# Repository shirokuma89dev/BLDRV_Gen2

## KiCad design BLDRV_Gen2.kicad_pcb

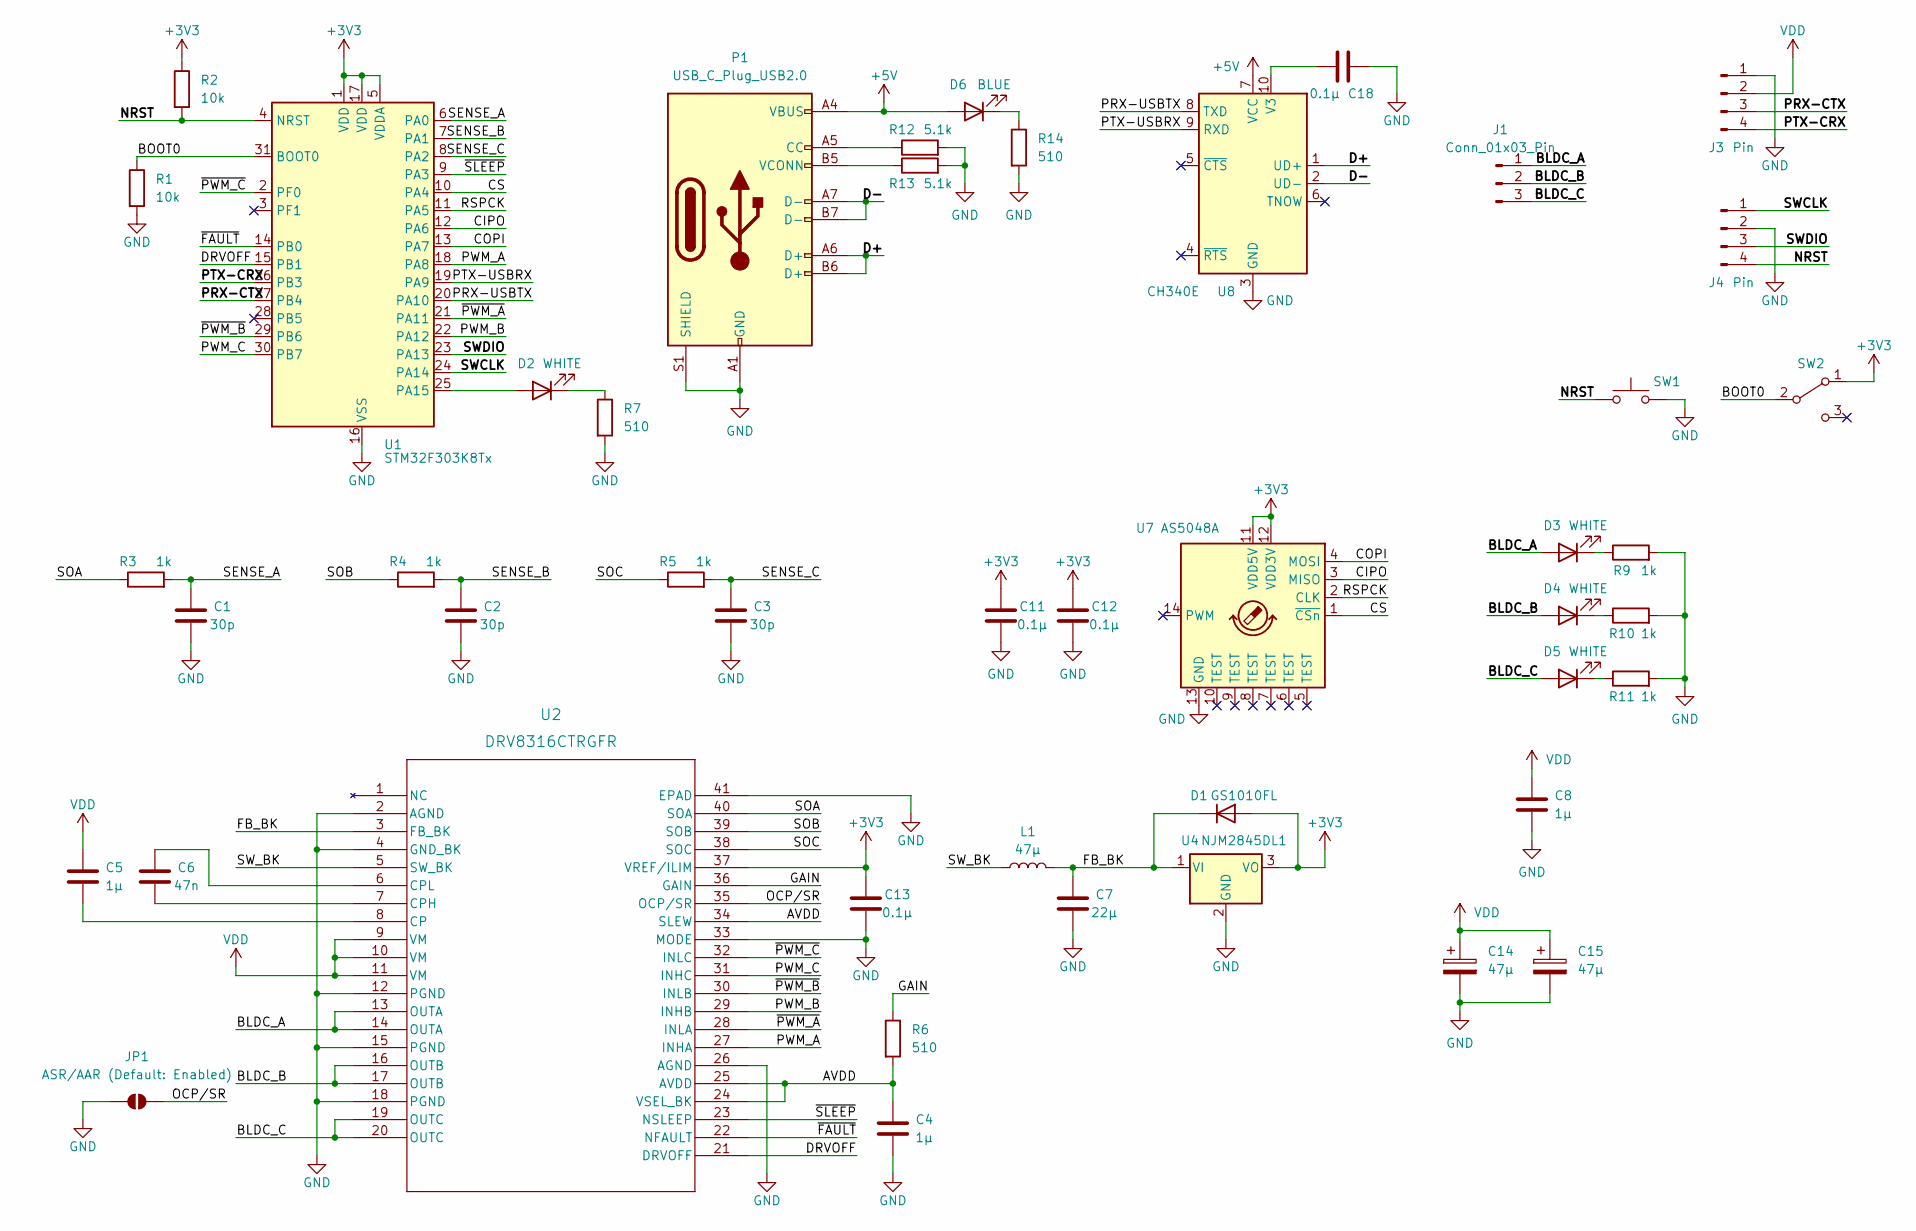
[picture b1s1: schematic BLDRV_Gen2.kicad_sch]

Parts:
C1, C2, C3: 30p; C_0603_1608Metric
C4, C5: 1μ; C_0603_1608Metric
C6: 47n; C_0603_1608Metric
C7: 22µ; C_0603_1608Metric
C8: 1µ; C_0603_1608Metric
C11, C12, C13, C18: 0.1µ; C_0603_1608Metric
C14, C15: 47μ; CP_Elec_5x5.3
D1: GS1010FL; D_SOD-123
D2, D3, D4, D5: WHITE; LED_0603_1608Metric
D6: BLUE; LED_0603_1608Metric
J1: Conn_01x03_Pin; Molex_SPOX_5268-03A_1x03_P2.50mm_Horizontal
J3: Pin; Molex_SPOX_5268-04A_1x04_P2.50mm_Horizontal
J4: Pin; PinHeader_1x04_P1.00mm_Vertical
JP1: ASR/AAR (Default: Enabled); SolderJumper-2_P1.3mm_Open_TrianglePad1.0x1.5mm
L1: 47μ; L_6.3x6.3_H3
P1: USB_C_Plug_USB2.0; USB_C_Receptacle_HCTL_HC-TYPE-C-16P-01A
R1, R2: 10k; R_0402_1005Metric
R3, R4, R5, R9, R10, R11: 1k; R_0402_1005Metric
R6, R7, R14: 510; R_0402_1005Metric
R12, R13: 5.1k; R_0402_1005Metric
SW1: SW_Push; SW_PUSH_6mm
SW2: SW_SPDT; SW_Slide_SPDT_Angled_CK_OS102011MA1Q
U1: STM32F303K8Tx; LQFP-32_7x7mm_P0.8mm
U2: DRV8316CTRGFR; VQFN40_RGF_TEX
U4: NJM2845DL1; TO-252-2
U7: AS5048A; TSSOP-14_4.4x5mm_P0.65mm
U8: CH340E; MSOP-10_3x3mm_P0.5mm

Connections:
+3V3: C11.2, C12.2, C13.2, D1.2 (A), R2.1, SW2.1 (A), U1.1 (VDD), U1.5 (VDDA), U1.17 (VDD), U2.37 (VREF/ILIM), U4.3 (VO), U7.11 (VDD5V), U7.12 (VDD3V)
+5V: D6.2 (A), P1.A4 (VBUS), P1.A9 (VBUS), P1.B4 (VBUS), P1.B9 (VBUS), U8.7 (VCC)
/AVDD: C4.2, R6.2, U2.24 (VSEL_BK), U2.25 (AVDD), U2.34 (SLEW)
/BLDC_A: D3.2 (A), J1.1, U2.13 (OUTA), U2.14 (OUTA)
/BLDC_B: D4.2 (A), J1.2, U2.16 (OUTB), U2.17 (OUTB)
/BLDC_C: D5.2 (A), J1.3, U2.19 (OUTC), U2.20 (OUTC)
/BOOT0: R1.1, SW2.2 (B), U1.31 (BOOT0)
/CIPO: U1.12 (PA6), U7.3 (MISO)
/COPI: U1.13 (PA7), U7.4 (MOSI)
/CS: U1.10 (PA4), U7.1 (~CSn)
/D+: P1.A6 (D+), P1.B6 (D+), U8.1 (UD+)
/D-: P1.A7 (D-), P1.B7 (D-), U8.2 (UD-)
/DRVOFF: U1.15 (PB1), U2.21 (DRVOFF)
/FB_BK: C7.2, D1.1 (K), L1.2, U2.3 (FB_BK), U4.1 (VI)
/GAIN: R6.1, U2.36 (GAIN)
/NRST: J4.4, R2.2, SW1.1, U1.4 (NRST)
/OCP/SR: JP1.2 (B), U2.35 (OCP/SR)
/PRX-CTX: J3.3, U1.27 (PB4)
/PRX-USBTX: U1.20 (PA10), U8.8 (TXD)
/PTX-CRX: J3.4, U1.26 (PB3)
/PTX-USBRX: U1.19 (PA9), U8.9 (RXD)
/PWM_A: U1.18 (PA8), U2.27 (INHA)
/PWM_B: U1.22 (PA12), U2.29 (INHB)
/PWM_C: U1.30 (PB7), U2.31 (INHC)
/RSPCK: U1.11 (PA5), U7.2 (CLK)
/SENSE_A: C1.2, R3.2, U1.6 (PA0)
/SENSE_B: C2.2, R4.2, U1.7 (PA1)
/SENSE_C: C3.2, R5.2, U1.8 (PA2)
/SOA: R3.1, U2.40 (SOA)
/SOB: R4.1, U2.39 (SOB)
/SOC: R5.1, U2.38 (SOC)
/SWCLK: J4.1, U1.24 (PA14)
/SWDIO: J4.3, U1.23 (PA13)
/SW_BK: L1.1, U2.5 (SW_BK)
/~FAULT: U1.14 (PB0), U2.22 (NFAULT)
/~PWM_A: U1.21 (PA11), U2.28 (INLA)
/~PWM_B: U1.29 (PB6), U2.30 (INLB)
/~PWM_C: U1.2 (PF0), U2.32 (INLC)
/~SLEEP: U1.9 (PA3), U2.23 (NSLEEP)
GND: C1.1, C2.1, C3.1, C4.1, C7.1, C8.1, C11.1, C12.1, C13.1, C14.2, C15.2, C18.2, J3.1, J4.2, JP1.1 (A), P1.A1 (GND), P1.A12 (GND), P1.B1 (GND), P1.B12 (GND), P1.S1 (SHIELD), R1.2, R7.2, R9.2, R10.2, R11.2, R12.2, R13.2, R14.2, SW1.2, U1.16 (VSS), U1.32 (VSS), U2.2 (AGND), U2.4 (GND_BK), U2.12 (PGND), U2.15 (PGND), U2.18 (PGND), U2.26 (AGND), U2.33 (MODE), U2.41 (EPAD), U4.2 (GND), U7.13 (GND), U8.3 (GND)
unnamed: D2.2 (A), U1.25 (PA15)
unnamed: D2.1 (K), R7.1
unnamed: D3.1 (K), R9.1
unnamed: D4.1 (K), R10.1
unnamed: D5.1 (K), R11.1
unnamed: D6.1 (K), R14.1
unnamed: P1.A5 (CC), R12.1
unnamed: P1.B5 (VCONN), R13.1
unnamed: C5.1, U2.8 (CP)
unnamed: C6.1, U2.7 (CPH)
unnamed: C6.2, U2.6 (CPL)
unnamed: C18.1, U8.10 (V3)
VDD: C5.2, C8.2, C14.1, C15.1, J3.2, U2.9 (VM), U2.10 (VM), U2.11 (VM)

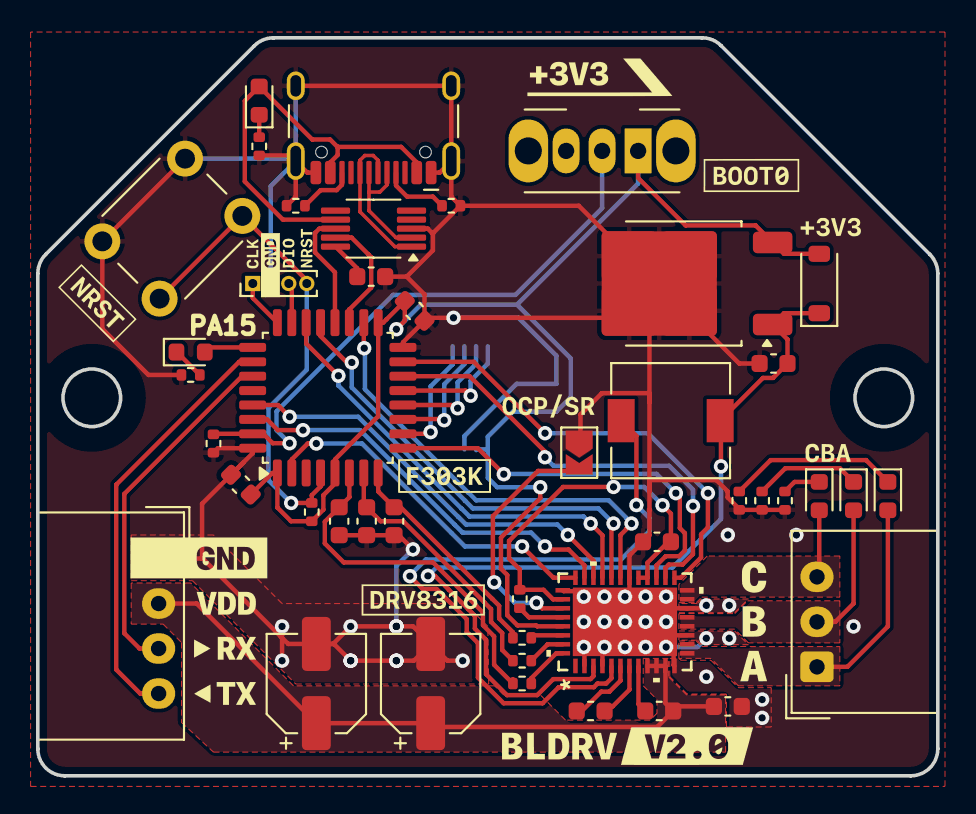
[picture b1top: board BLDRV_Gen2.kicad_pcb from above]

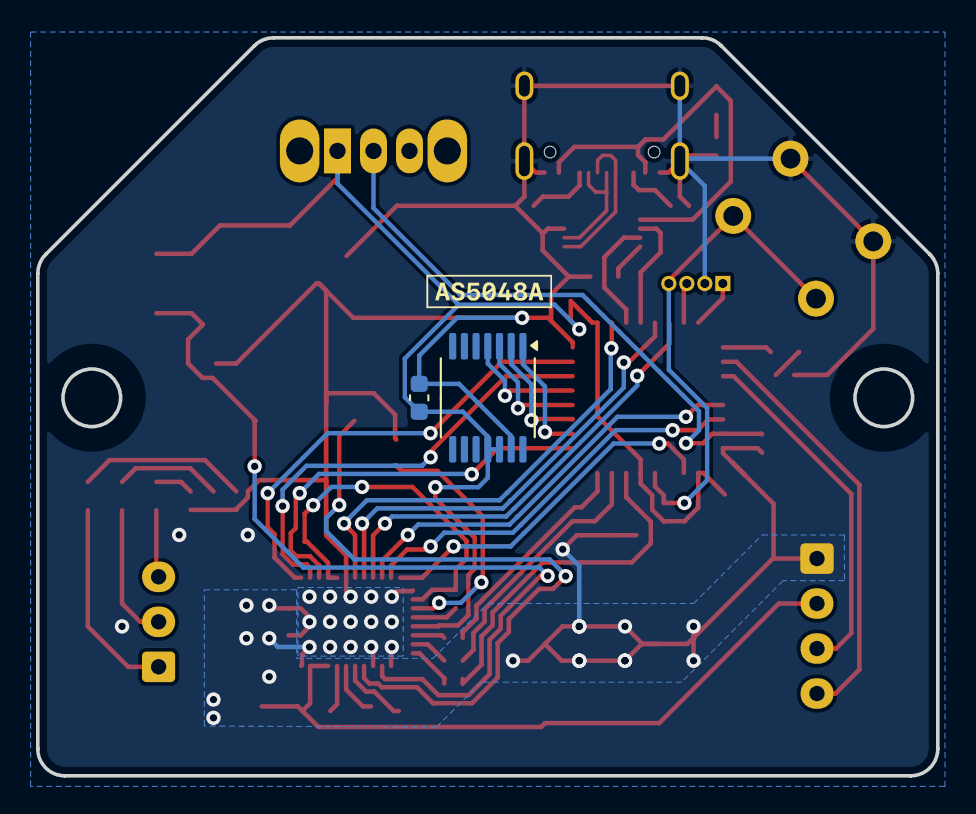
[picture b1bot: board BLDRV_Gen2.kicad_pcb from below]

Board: 2 copper layers, 50.0 x 41.0 mm, 46 parts (2 on the bottom side), 53 nets.

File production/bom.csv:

Designator,Footprint,Quantity,Value,LCSC Part #
"C1, C2, C3",0603,3,30p,
"C11, C12, C13, C18",0603,4,0.1µ,
"C14, C15",CP_Elec_5x5.3,2,47μ,
"C4, C5, C8",0603,3,1μ,
C6,0603,1,47n,
C7,0603,1,22µ,
D1,D_SOD-123,1,GS1010FL,
"D2, D3, D4, D5",0603,4,WHITE,
D6,0603,1,BLUE,
J1,Molex_SPOX_5268-03A_1x03_P2.50mm_Horizontal,1,Conn_01x03_Pin,
J3,Molex_SPOX_5268-04A_1x04_P2.50mm_Horizontal,1,Pin,
J4,PinHeader_1x04_P1.00mm_Vertical,1,Pin,
L1,L_6.3x6.3_H3,1,47μ,
P1,USB_C_Receptacle_HCTL_HC-TYPE-C-16P-01A,1,USB_C_Plug_USB2.0,
"R1, R2",0402,2,10k,
"R10, R11, R3, R4, R5, R9",0402,6,1k,
"R12, R13",0402,2,5.1k,
"R14, R6, R7",0402,3,510,
SW1,SW_PUSH_6mm,1,SW_Push,
SW2,SW_Slide_SPDT_Angled_CK_OS102011MA1Q,1,SW_SPDT,
U1,LQFP-32_7x7mm_P0.8mm,1,STM32F303K8Tx,
U2,VQFN40_RGF_TEX,1,DRV8316CTRGFR,
U4,TO-252-2,1,NJM2845DL1,
U7,TSSOP-14_4.4x5mm_P0.65mm,1,AS5048A,
U8,MSOP-10_3x3mm_P0.5mm,1,CH340E,

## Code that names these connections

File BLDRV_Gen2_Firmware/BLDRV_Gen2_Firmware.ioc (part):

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Mcu.Name=STM32F303K(6-8)Tx
Mcu.Package=LQFP32
Mcu.UserName=STM32F303K8Tx
PA0.Mode=IN1-Single-Ended
PA0.Signal=ADC1_IN1
PA1.Mode=IN2-Single-Ended
PA1.Signal=ADC1_IN2
PA10.Mode=Asynchronous
PA10.Signal=USART1_RX
PA11.GPIOParameters=GPIO_Speed,GPIO_Label
PA11.GPIO_Label=PWM_A_L
PA11.GPIO_Speed=GPIO_SPEED_FREQ_HIGH
PA11.Mode=PWM Generation1 CH1 CH1N
PA11.Signal=TIM1_CH1N
PA12.GPIOParameters=GPIO_Speed,GPIO_Label
PA12.GPIO_Label=PWM_B_H
PA12.GPIO_Speed=GPIO_SPEED_FREQ_HIGH
PA12.Signal=S_TIM16_CH1
PA13.GPIOParameters=GPIO_Label
PA13.GPIO_Label=SWDIO
PA13.Mode=Serial_Wire
PA13.Signal=SYS_JTMS-SWDIO
PA14.GPIOParameters=GPIO_Label
PA14.GPIO_Label=SWCLK
PA14.Mode=Serial_Wire
PA14.Signal=SYS_JTCK-SWCLK
PA15.Signal=S_TIM2_CH1_ETR
PA2.Mode=IN3-Single-Ended
PA2.Signal=ADC1_IN3
PA4.Signal=GPIO_Output
PA5.Mode=Full_Duplex_Master
PA5.Signal=SPI1_SCK
PA6.Mode=Full_Duplex_Master
PA6.Signal=SPI1_MISO
PA7.Mode=Full_Duplex_Master
PA7.Signal=SPI1_MOSI
PA8.GPIOParameters=GPIO_Speed,GPIO_Label
PA8.GPIO_Label=PWM_A_H
PA8.GPIO_Speed=GPIO_SPEED_FREQ_HIGH
PA8.Signal=S_TIM1_CH1
PA9.Mode=Asynchronous
PA9.Signal=USART1_TX
PB1.GPIOParameters=GPIO_Label
PB1.GPIO_Label=DRVOFF
PB1.Signal=GPIO_Output
PB3.Mode=Asynchronous
PB3.Signal=USART2_TX
PB4.Mode=Asynchronous
PB4.Signal=USART2_RX
PB6.GPIOParameters=GPIO_FM6,GPIO_Speed,GPIO_Label
PB6.GPIO_FM6=SYSCFG_CFGR1_I2C_PB6_FMP
PB6.GPIO_Label=PWM_B_L
PB6.GPIO_Speed=GPIO_SPEED_FREQ_HIGH
PB6.Mode=PWM Generation1 CH1 CH1N
PB6.Signal=TIM16_CH1N
PB7.GPIOParameters=GPIO_Label
PB7.GPIO_Label=PWM_C_H
PB7.Signal=S_TIM3_CH4
PF0\ /\ OSC_IN.GPIOParameters=GPIO_Speed,GPIO_Label
PF0\ /\ OSC_IN.GPIO_Label=PWM_C_L
PF0\ /\ OSC_IN.GPIO_Speed=GPIO_SPEED_FREQ_HIGH
PF0\ /\ OSC_IN.Mode=PWM Generation3 CH3N
PF0\ /\ OSC_IN.Signal=TIM1_CH3N
RCC.HSEPLLFreq_Value=8000000
RCC.HSE_VALUE=8000000
RCC.SYSCLKFreq_VALUE=32000000
RCC.SYSCLKSourceVirtual=RCC_SYSCLKSOURCE_PLLCLK
board=NUCLEO-F303K8
boardIOC=true

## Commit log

2024-09-28 ✅ 正弦波駆動
2024-09-28 ✨ q軸電圧一定制御
2024-09-28 ⚡️ 角度系を変更
2024-09-28 🐛 キャリブレーションの角度系
2024-09-28 💩 ゴミベクトル制御
2024-09-29 💩 q軸電流のこと誰が好きなん？
2024-09-29 ✅ もうどうでも良くなった
2024-09-29 ♻️ 回路図
2024-10-03 ✅ 動くプログラム
2024-10-03 ⚡️ バッファを2->4byteに変更
